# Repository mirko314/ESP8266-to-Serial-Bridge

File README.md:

# ESP8266-to-Serial-Bridge
PCB Design for faster Programming of the ESP8266 using a Serial-Usb Adaptor
The ESP8266 Chip can be programmed through Serial.

Taking Inspiration from http://arduino-hannover.de/2015/04/08/arduino-ide-mit-dem-esp8266/ this PCB uses a slightly different USB-to-Serial Brisge. The PCB does Break Out the Pins and enables the user to program the Module easily.

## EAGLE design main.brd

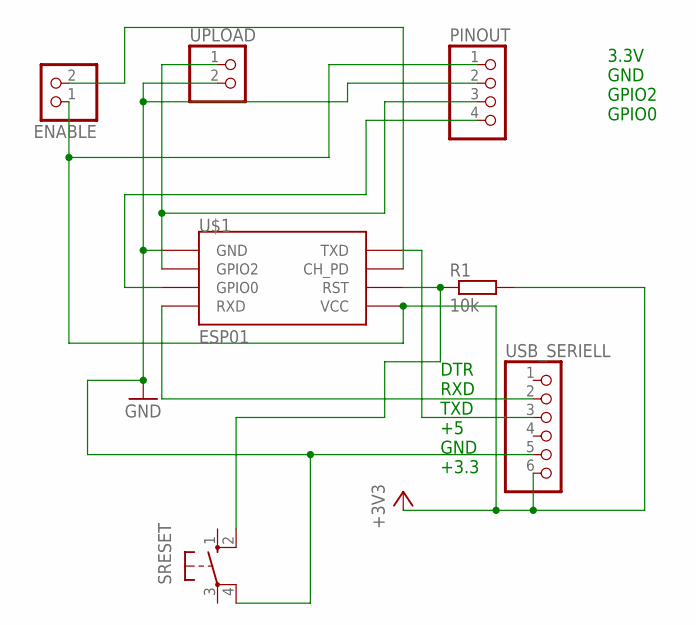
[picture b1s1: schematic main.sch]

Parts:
ENABLE: PINHD-1X2; 1X02
PINOUT: PINHD-1X4; 1X04
R1: 10k; 0207/10
SRESET: 10-XX; B3F-10XX
U$1: ESP01
UPLOAD: PINHD-1X2; 1X02
USB_SERIELL: PINHD-1X6; 1X06

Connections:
+3V3: ENABLE.1, PINOUT.1, R1.2, U$1.VCC, USB_SERIELL.6
GND: PINOUT.2, SRESET.4 (P1), U$1.GND, UPLOAD.2, USB_SERIELL.5
unnamed: U$1.RX (RXD), USB_SERIELL.2
unnamed: U$1.TX (TXD), USB_SERIELL.3
unnamed: PINOUT.3, U$1.GPIO2, UPLOAD.1
unnamed: PINOUT.4, U$1.GPIO0
unnamed: R1.1, SRESET.2 (S1), U$1.RST
unnamed: ENABLE.2, U$1.CH_PD

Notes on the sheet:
DTR RXD TXD +5 GND +3.3
3.3V GND GPIO2 GPIO0

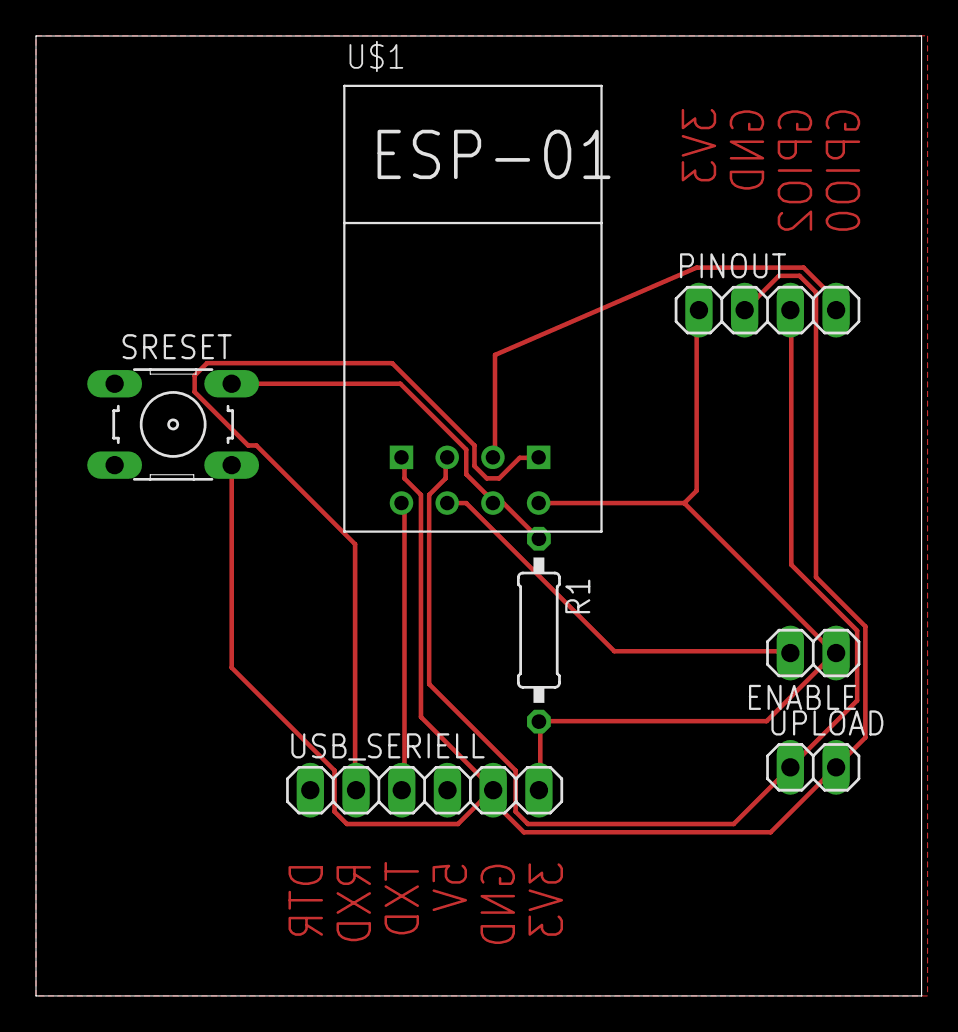
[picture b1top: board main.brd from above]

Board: 2 copper layers, 49.2 x 53.3 mm, 7 parts (0 on the bottom side), 8 nets.

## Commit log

2015-06-23 :space_invader: Added .gitattributes & .gitignore files
2015-06-23 First check-in
    Upload of the first files.
